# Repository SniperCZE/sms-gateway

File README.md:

# sms-gateway
Open source / open hardware multiline SMS gateway with HTTP api and RabbitMQ consumer, enclosed in nice 1U custom case.

## Work in progress!

This repo is under development. There is no guarantee that any part of it will not change in the future. Models, schemas and part lists are not final.

## Idea

I would like to have SMS gateway for sending SMS, which:
- receives messages with HTTP API or RabbitMQ queue
- works without active Internet connection
- can be scaled up, can be HA
- looks good
- is not expensive

## Electronics

Whole idea is based on raspberry pi minicomputers with SIM800L GSM modules and some custom PCBs. All schematics are KiCAD (https://kicad.org/) projects.

### Power
I'am using one input of 230V AC, converted to 5V DC for every components. There is custom designed PDU board inside of gateway interconnecting all components. Ethernet switch, thermometer and raspberries are powered directly with 5V, GSM module SIM800L must be powered with 4.3V, so I'm using basic diode 1N4007 to drop 5V to 4.3V.

## Mechanics

I will have to build custom 1U rack case for this project. You can find here models ad FreeCAD (https://www.freecadweb.org/) project.

FreeCAD workbenches needed:
- `KiCadStepUp` - integration of KiCAD
- `Fasteners` - screws and nuts
- `Sheet metal` - Support of metal sheet bending
- `Exploded assembly` - Generation of assembly animation

## Software

Every piece of software for my gateway is written in python with some bash scripts and systemd units.

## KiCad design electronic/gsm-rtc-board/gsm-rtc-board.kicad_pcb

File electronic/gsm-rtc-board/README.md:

# GSM + RTC board

This board handles RTC and GSM modules, connects them to Raspberry and provide power for modules and Raspberry

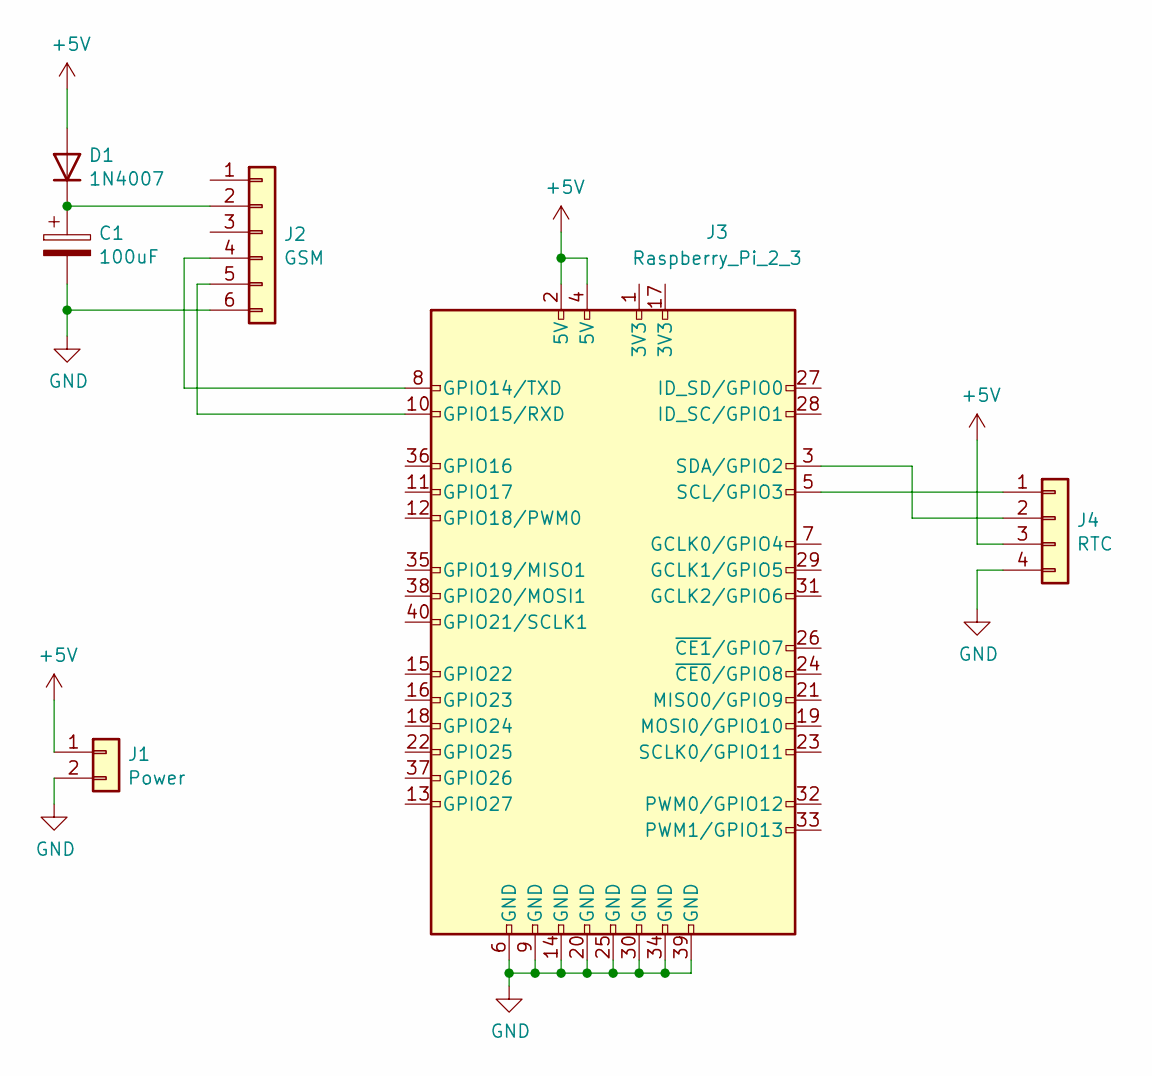
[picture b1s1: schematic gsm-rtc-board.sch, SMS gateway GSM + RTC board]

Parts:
C1: 100uF; CP_Radial_D6.3mm_P2.50mm
D1: 1N4007; D_DO-41_SOD81_P10.16mm_Horizontal
J1: Power; TerminalBlock_Phoenix_MKDS-3-2-5.08_1x02_P5.08mm_Horizontal
J2: GSM; PinSocket_1x06_P2.54mm_Vertical
J3: Raspberry_Pi_2_3; PinHeader_2x20_P2.54mm_Vertical
J4: RTC; PinSocket_1x04_P2.54mm_Vertical

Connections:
+5V: D1.2 (A), J1.1, J3.2 (5V), J3.4 (5V), J4.3
GND: C1.2, J1.2, J2.6, J3.6 (GND), J3.9 (GND), J3.14 (GND), J3.20 (GND), J3.25 (GND), J3.30 (GND), J3.34 (GND), J3.39 (GND), J4.4
unnamed: C1.1, D1.1 (K), J2.2
unnamed: J2.4, J3.8 (GPIO14/TXD)
unnamed: J2.5, J3.10 (GPIO15/RXD)
unnamed: J3.3 (SDA/GPIO2), J4.2
unnamed: J3.5 (SCL/GPIO3), J4.1

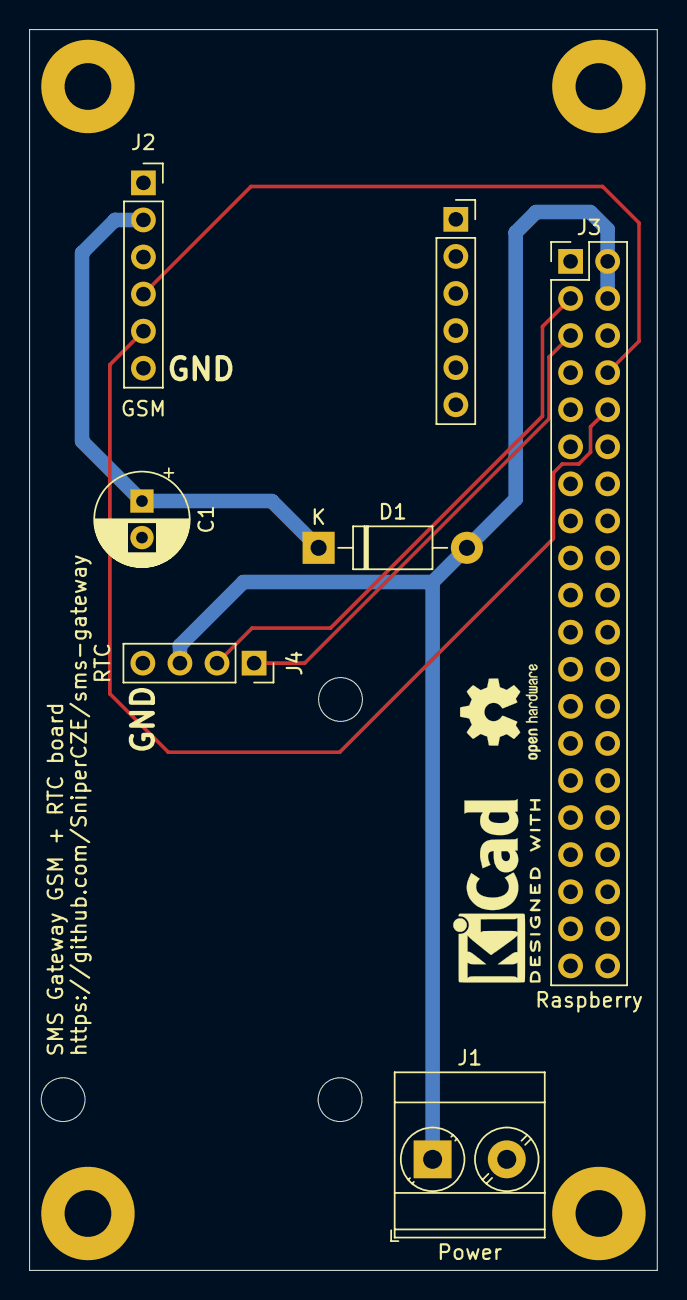
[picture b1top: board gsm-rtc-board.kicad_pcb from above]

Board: 2 copper layers, 43.0 x 85.0 mm, 6 parts (0 on the bottom side), 7 nets.

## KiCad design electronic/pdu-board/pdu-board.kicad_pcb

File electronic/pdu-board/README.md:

# PDU board

This board is used for distribution of +5V and GND across all parts of gateway.

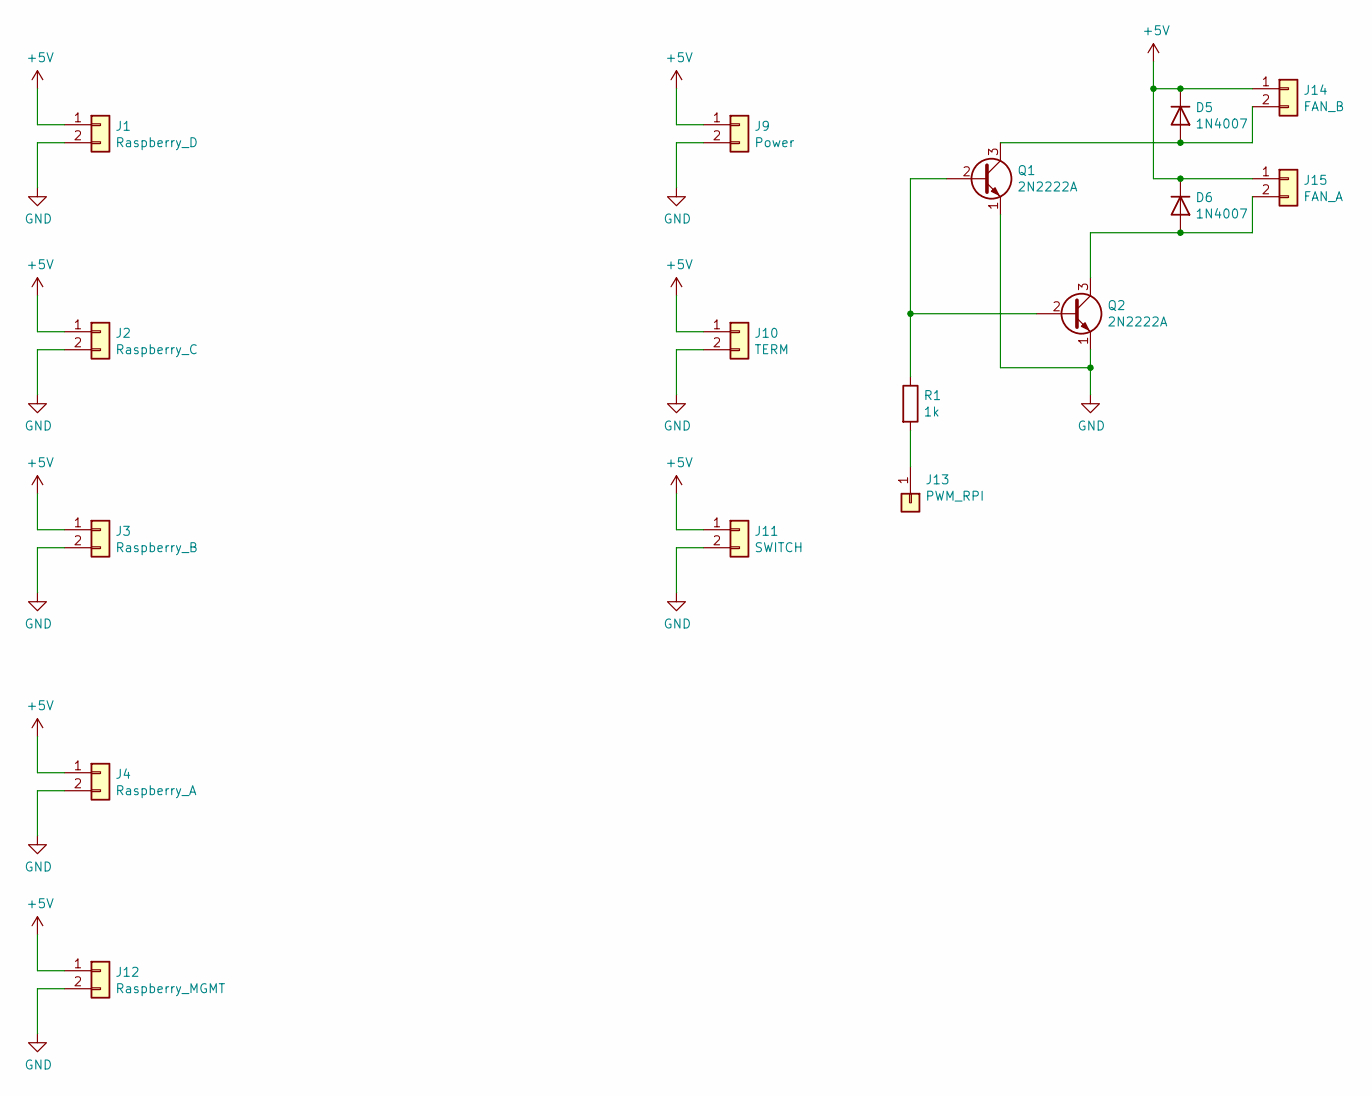
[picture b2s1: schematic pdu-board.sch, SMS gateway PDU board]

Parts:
D5, D6: 1N4007; D_DO-41_SOD81_P10.16mm_Horizontal
J1: Raspberry_D; TerminalBlock_Phoenix_MKDS-3-2-5.08_1x02_P5.08mm_Horizontal
J2: Raspberry_C; TerminalBlock_Phoenix_MKDS-3-2-5.08_1x02_P5.08mm_Horizontal
J3: Raspberry_B; TerminalBlock_Phoenix_MKDS-3-2-5.08_1x02_P5.08mm_Horizontal
J4: Raspberry_A; TerminalBlock_Phoenix_MKDS-3-2-5.08_1x02_P5.08mm_Horizontal
J9: Power; TerminalBlock_Phoenix_MKDS-3-2-5.08_1x02_P5.08mm_Horizontal
J10: TERM; TerminalBlock_Phoenix_MKDS-3-2-5.08_1x02_P5.08mm_Horizontal
J11: SWITCH; TerminalBlock_Phoenix_MKDS-3-2-5.08_1x02_P5.08mm_Horizontal
J12: Raspberry_MGMT; TerminalBlock_Phoenix_MKDS-3-2-5.08_1x02_P5.08mm_Horizontal
J13: PWM_RPI; PinHeader_1x01_P2.54mm_Vertical
J14: FAN_B; TerminalBlock_Phoenix_MKDS-3-2-5.08_1x02_P5.08mm_Horizontal
J15: FAN_A; TerminalBlock_Phoenix_MKDS-3-2-5.08_1x02_P5.08mm_Horizontal
Q1, Q2: 2N2222A; TO-18-3
R1: 1k; R_Axial_DIN0309_L9.0mm_D3.2mm_P15.24mm_Horizontal

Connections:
+5V: D5.1 (K), D6.1 (K), J1.1, J2.1, J3.1, J4.1, J9.1, J10.1, J11.1, J12.1, J14.1, J15.1
GND: J1.2, J2.2, J3.2, J4.2, J9.2, J10.2, J11.2, J12.2, Q1.1 (E), Q2.1 (E)
unnamed: D5.2 (A), J14.2, Q1.3 (C)
unnamed: D6.2 (A), J15.2, Q2.3 (C)
unnamed: J13.1, R1.2
unnamed: Q1.2 (B), Q2.2 (B), R1.1

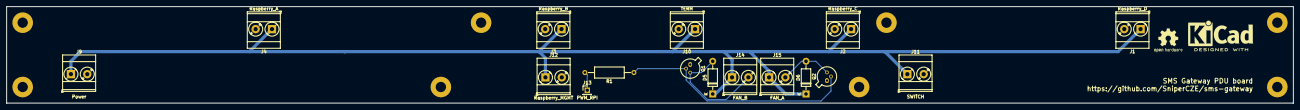
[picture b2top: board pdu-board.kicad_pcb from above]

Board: 2 copper layers, 400.0 x 30.0 mm, 16 parts (0 on the bottom side), 6 nets.

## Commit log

2021-03-30 PDU board schematic
2021-03-31 PDU board schematic project
2021-04-06 Readme + repo structure
2021-04-06 PDU readme
2021-04-08 RTC + GSM board
2021-04-08 rtc mounting holes
2021-04-08 Rack case WIP
2021-04-17 GSM sockets slightly off
2021-04-17 New 3D render
2021-04-18 Block diagram for power
2021-04-18 typo
2021-04-18 translate fix
2021-04-18 List of FreeCAD addons
